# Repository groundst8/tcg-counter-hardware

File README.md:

# TCG Counter Hardware

## Components

[TI RF430FRL152H](https://www.ti.com/lit/ds/symlink/rf430frl152h.pdf?ts=1718074976833&ref_url=https%253A%252F%252Fwww.ti.com%252Fproduct%252FRF430FRL152H)
- ISO 15693
- NfcV
- 1.5V passivey powered
- 8 bit GPIO
- I2c
- +/- 400 uA GPIO current, 500 uA max all I/O 0.15V voltage drop

[Ynvisible D0432G02V01](https://assets-global.website-files.com/5f7f21e12602d912658dce12/62207f04e89fc72369fa582a_D0432G02V01-V1.0.pdf)
- 7 Segment E-Paper Display
- +/- 1.5V operating voltage
- 0.81 uA steady state current, all segments on
- ~3.25 mA (datasheet says 2.92 mA) peak current all segments; ~1.25 mA peak / segment

[TI TCAL9539](https://www.ti.com/lit/ds/symlink/tcal9539.pdf)
- Low-Voltage 16-Bit I2c Expander
- I/Os backpowered protected

## Constraints

### Harvested Power

Table 4 from [Frequently asked questions for RF430FRL15xH devices](https://www.ti.com/lit/an/sloa247c/sloa247c.pdf) shows the maximum harvested power available when using the using the TRF7970AEVM with a 5-V power supply as the tag reader. It is also mentioned that the current that can be supplied depends on the reader distance to the tag. 

## Ynvisible Display Testing

Twenty minute timelapse test to evaluation if the Ynvisible 7 segment display keeps readable contrast over a 20 minute period without power. Twenty minutes was chosen as the upper end of how long a counter would go without being updated. Twenty minutes is the length of the average Magic The Gathering standard format game. Commander games go longer but generally counters are updated over the course of the game which would provide the refresh without requiring additional effort.

## Development Board Prototyping

### Iteration 1

- GoodTag11
  - Open source hardware design
  - PCB & SMT assembly by JLCPCB
  - Through hole headers hand soldered by yours truly
- Ynvisible E-Paper Display Kit Adapter

#### Issues
- E-paper display backpowering RF430FRL152H via GPIO ESD diodes in no power state
  - GPIOs do not remain high-Z and display loses contrast
- TimerA0 low power delays not working in ROM patch operating mode
  - Temporarily doing delays on smartphone side
 
## Iteration 2

- Put two 4 channel TMUX1511 analog switches between GPIOs and display
  - Enabled when have power and disabled when no power is applied
  - Fixes display contrast loss issue from Iteration 1

#### Issues
- GPIO Port1.7 is used by ROM code to indicate operating mode and doesn't seem available for display use in ROM patch mode
- Ultimately would be more useful with two 7 segment digits, could potentially use single chip TCAL9539 GPIO expanded that should also remain high-Z with no power
  - Would be fewer parts than the TMUX1511 solution and give greater capability
- Peak current consumption of display was more than anticiapted per segment
  - Look into handling larger peak current with appropriately sized capacitor

Ynvisible provided segment switching current decay curves which are shown below modeled with exponential decay functions. The raw data is available in 1vs7segs.xlsx. I was anticipating the single segment switching current to be lower so will need to do some additional testing and measurement to determine if enough energy will be harvested to do the switching.

## Iteration 3

- Switched to RF430FRL152HEVM dev board
  - Can program with MSP-FET programmer via JTAG
  - Work around issue programming GoodTag11 with GoodV over the air not working with NFC only ROM firmware
- Switched from TMUX1511s to TCAL9539 for GPIO expansion and backpower protection
- Switched to Ynvisible 2 digit 7 segment display

#### Issues
- Currently powered from MSP-FET source
  - Need to do testing and see if can find solution to passively power from RF field in a way that is economically viable
- Need to get JTAG level transalation working so can switch back to GoodTag11 and custom PCB instead of dev board and use MSP-FET programmer

## Iteration 4

- Switched back to GoodTag11 from RF430FRL152HEVM dev board
- JTAG Level Translation & JTAG debugging working
  - Using SN74AXC4T774 Evaluation Module with TCK, TDI, TMS, TDO, and RST signals 3.3v <-> 1.5v
  - Replaced some 10pF capacitors that should have been 10nF and were preventing JTAG debugging from working
- EnergyTrace working

#### Issues
- Evaluate passive power ability to drive display
- Complete PCB layouts for mainboard and JTAG translation board

## Iteration 5 - v1.0.0

### JLCPCB PCB with rails/fiducials for assembly

### Board with display attached and functioning

#### Issues
- Forgot pull-up resistors for RESET and INT pins on TCAL
- Firmware updating all segments in parallel is causing brownouts, look into sequential segment updating

## Electrical Engineering

[Jupyter Notebook](display.ipynb)

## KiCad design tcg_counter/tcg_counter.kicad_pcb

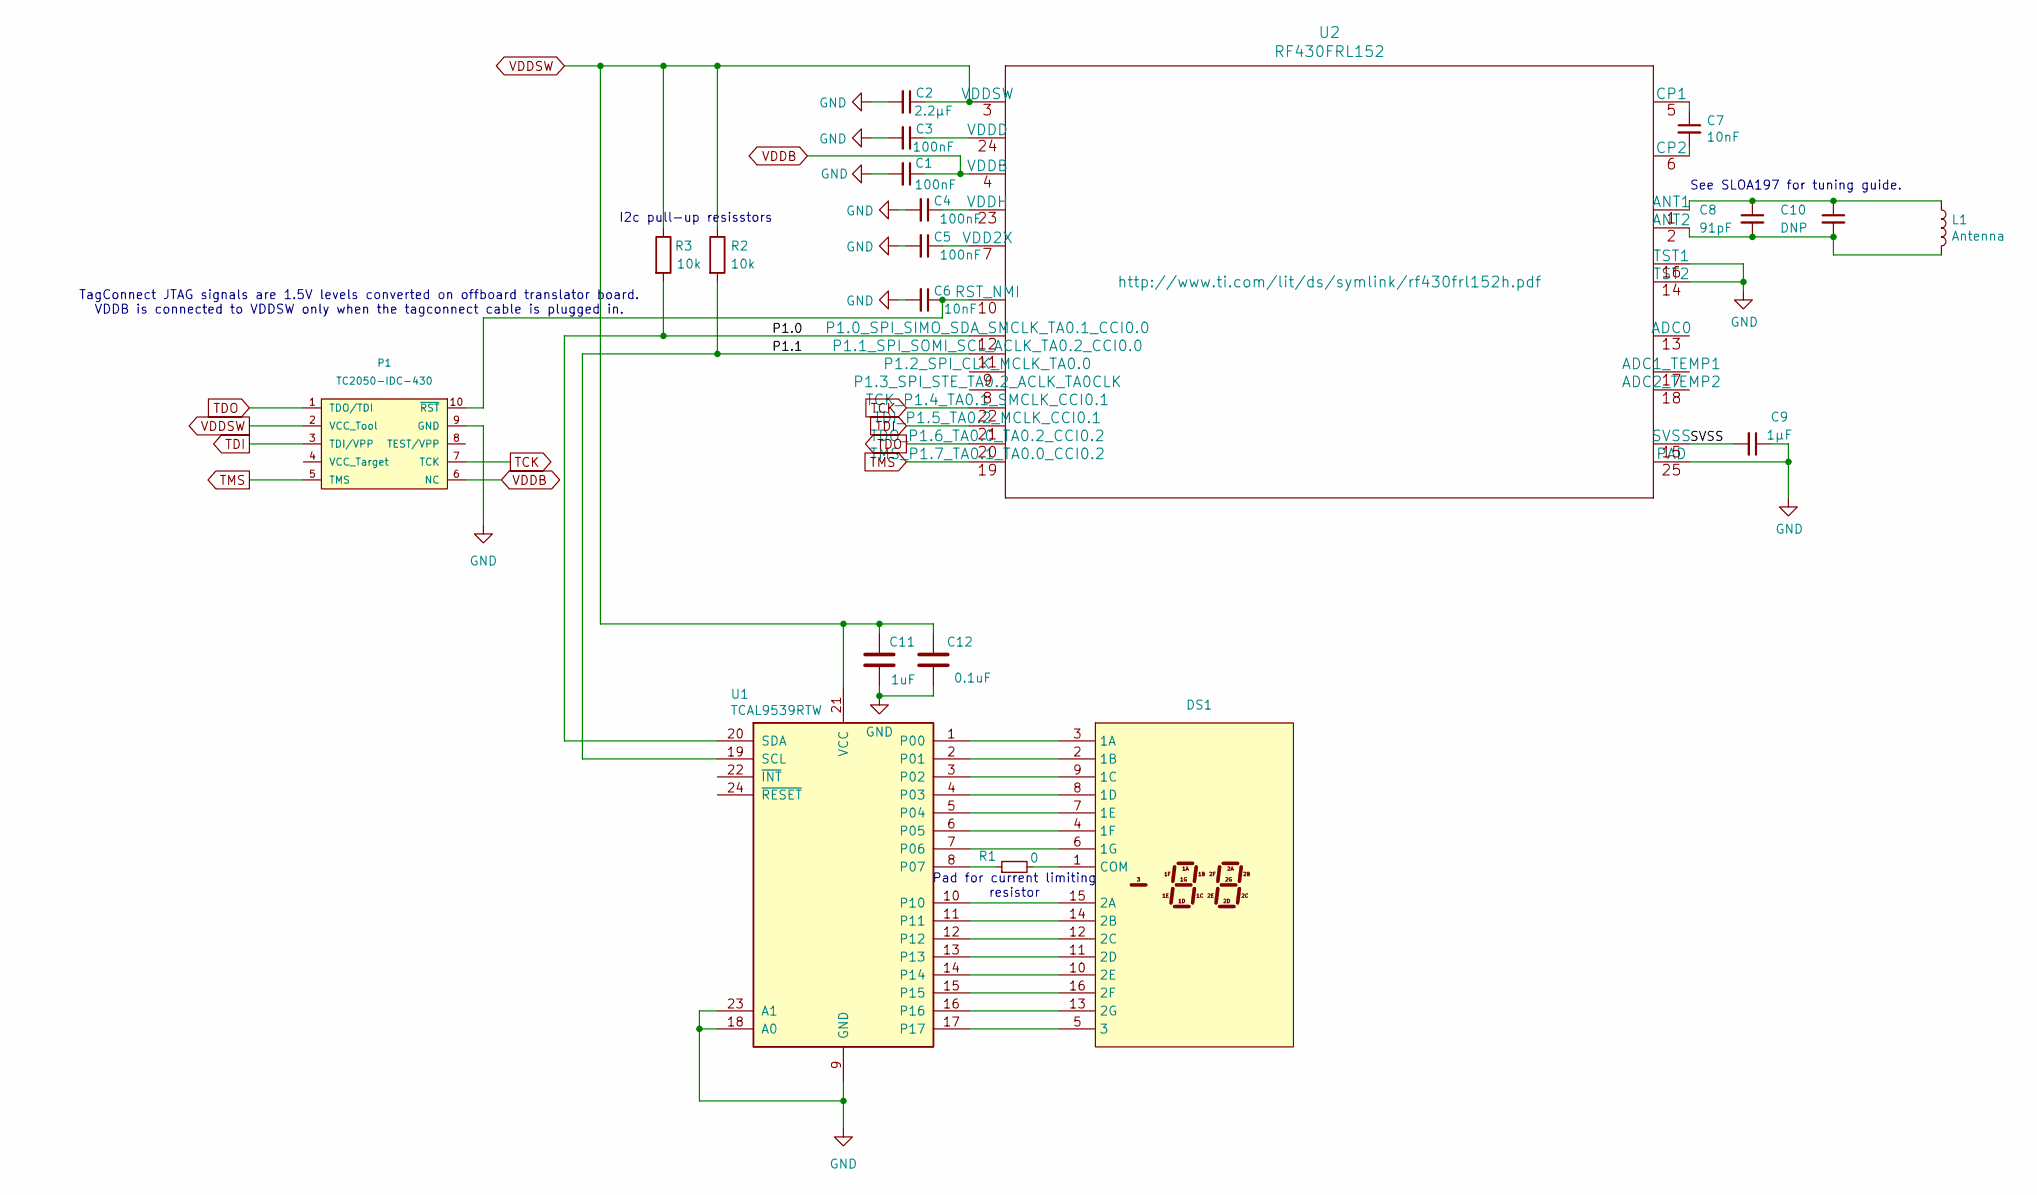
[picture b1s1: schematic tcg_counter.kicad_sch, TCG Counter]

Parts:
C1, C3, C4, C5: 100nF; C_0402_1005Metric
C2: 2.2µF; C_0402_1005Metric
C6, C7: 10nF; C_0402_1005Metric
C8: 91pF; C_0402_1005Metric
C9: 1µF; C_0402_1005Metric
C10: DNP; C_0402_1005Metric
C11: 1uF; C_0402_1005Metric
C12: 0.1uF; C_0402_1005Metric
DS1: D0430G02V01
L1: Antenna; GW10ANT
P1: TC2050-IDC-430; Tag-Connect_TC2050-IDC-NL_2x05_P1.27mm_Vertical_with_bottom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
R1: 0; R_0402_1005Metric
R2, R3: 10k; R_0402_1005Metric
U1: TCAL9539RTW; TI_RTW24_4x4mm_EP2.2mm
U2: RF430FRL152; RF430FRL152H

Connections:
/P1.0: R3.2, U1.20 (SDA), U2.12 (P1.0_SPI_SIMO_SDA_SMCLK_TA0.1_CCI0.0)
/P1.1: R2.2, U1.19 (SCL), U2.11 (P1.1_SPI_SOMI_SCL_ACLK_TA0.2_CCI0.0)
/SVSS: C9.2, U2.15 (SVSS)
GND: C1.2, C2.2, C3.2, C4.2, C5.2, C6.2, C9.1, C11.2, C12.2, P1.9 (GND), U1.9 (GND), U1.18 (A0), U1.23 (A1), U1.25, U2.14 (TST2), U2.16 (TST1), U2.25 (PAD)
unnamed: DS1.3 (1A), U1.1 (P00)
unnamed: DS1.2 (1B), U1.2 (P01)
unnamed: DS1.9 (1C), U1.3 (P02)
unnamed: DS1.8 (1D), U1.4 (P03)
unnamed: DS1.7 (1E), U1.5 (P04)
unnamed: DS1.4 (1F), U1.6 (P05)
unnamed: DS1.6 (1G), U1.7 (P06)
unnamed: DS1.15 (2A), U1.10
unnamed: DS1.14 (2B), U1.11
unnamed: DS1.12 (2C), U1.12
unnamed: DS1.11 (2D), U1.13
unnamed: DS1.10 (2E), U1.14
unnamed: DS1.16 (2F), U1.15
unnamed: DS1.13 (2G), U1.16
unnamed: DS1.5 (3), U1.17
unnamed: DS1.1 (COM), R1.2
unnamed: C6.1, P1.10 (~RST), U2.10 (RST_NMI)
unnamed: R1.1, U1.8 (P07)
unnamed: C8.1, C10.1, L1.1, U2.1 (ANT1)
unnamed: C8.2, C10.2, L1.2, U2.2 (ANT2)
unnamed: C7.1, U2.5 (CP1)
unnamed: C7.2, U2.6 (CP2)
unnamed: C5.1, U2.7 (VDD2X)
unnamed: C3.1, U2.24 (VDDD)
unnamed: C4.1, U2.23 (VDDH)
TCK: P1.7 (TCK), U2.22 (TCK_P1.4_TA0.1_SMCLK_CCI0.1)
TDI: P1.3 (TDI/VPP), U2.21 (TDI_P1.5_TA0.2_MCLK_CCI0.1)
TDO: P1.1 (TDO/TDI), U2.20 (TDO_P1.6_TA0.0_TA0.2_CCI0.2)
TMS: P1.5 (TMS), U2.19 (TMS_P1.7_TA0.1_TA0.0_CCI0.2)
VDDB: C1.1, P1.6 (NC), U2.4 (VDDB)
VDDSW: C2.1, C11.1, C12.1, P1.2 (VCC_Tool), R2.1, R3.1, U1.21 (VCC), U2.3 (VDDSW)

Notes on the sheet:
Pad for current limiting resistor
I2c pull-up resisstors
TagConnect JTAG signals are 1.5V levels converted on offboard translator board. VDDB is connected to VDDSW only when the tagconnect cable is plugged in.
See SLOA197 for tuning guide.

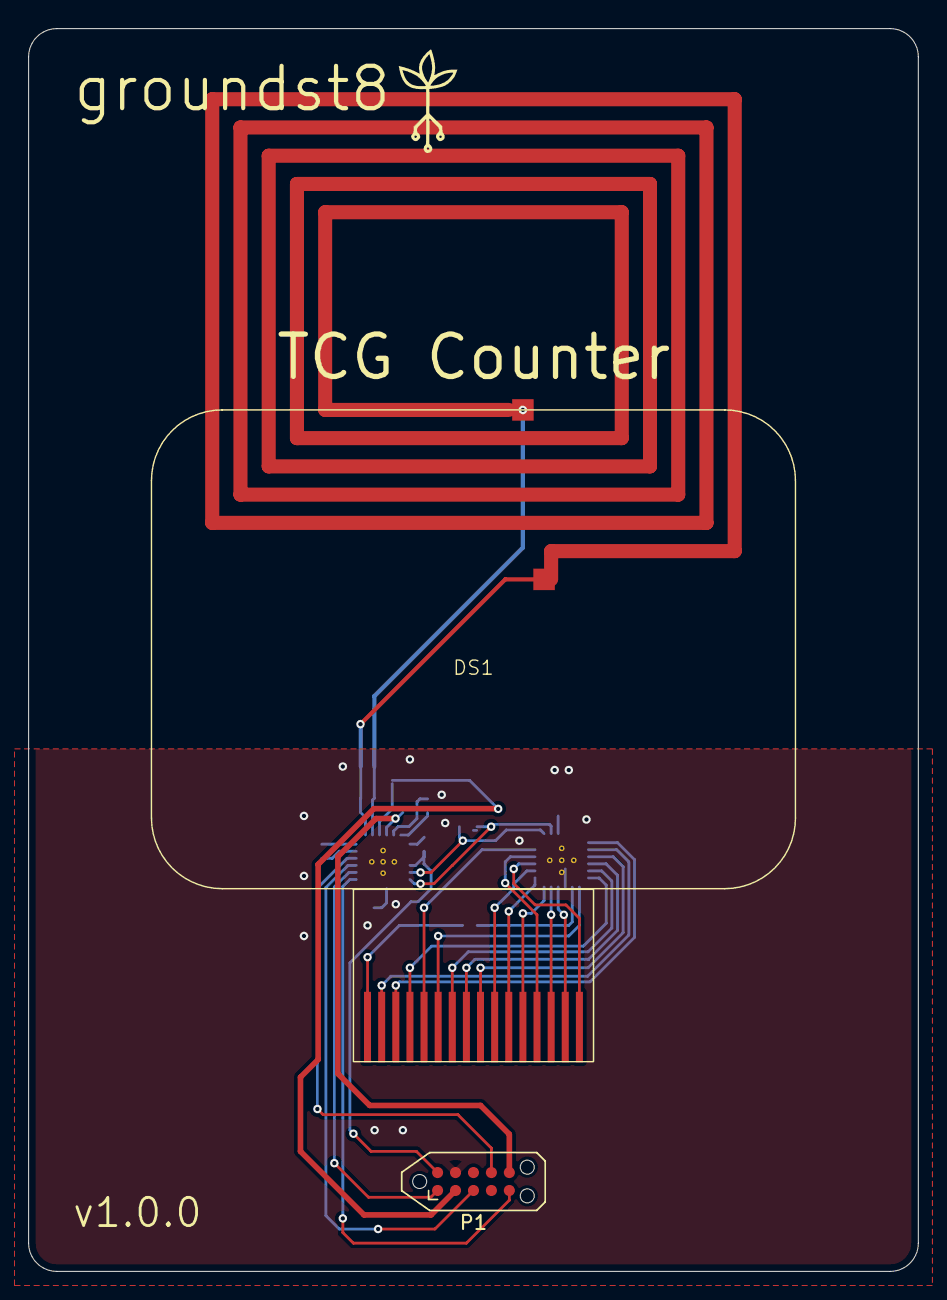
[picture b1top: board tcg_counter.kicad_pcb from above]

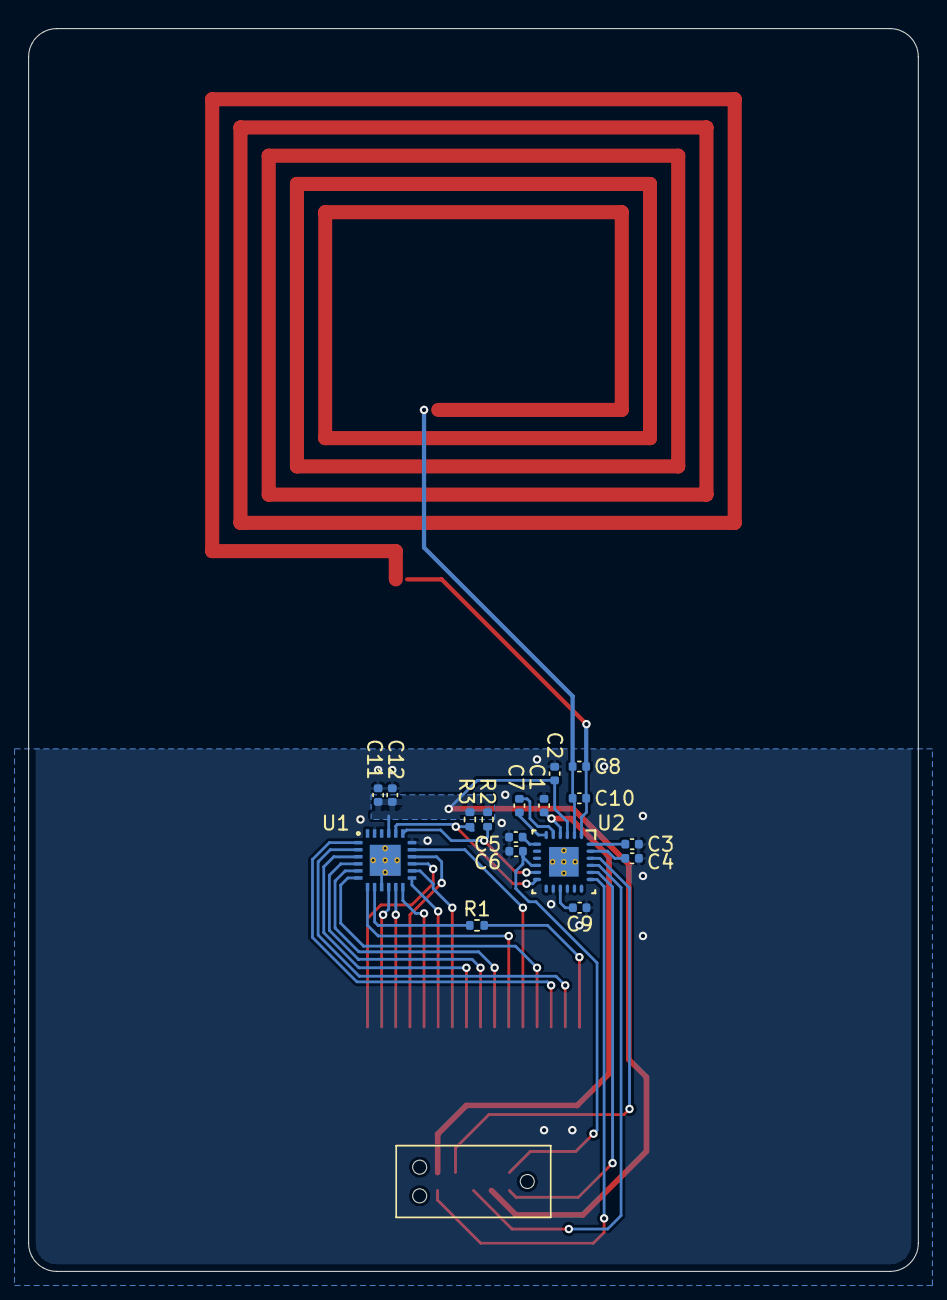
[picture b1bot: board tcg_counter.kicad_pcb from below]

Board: 2 copper layers, 63.0 x 88.0 mm, 20 parts (17 on the bottom side), 35 nets.

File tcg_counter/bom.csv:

"Reference","Value","Datasheet","Footprint","Qty","DNP"
"C1,C3,C4,C5","100nF","~","Capacitor_SMD:C_0402_1005Metric","4",""
"C2","2.2µF","~","Capacitor_SMD:C_0402_1005Metric","1",""
"C6,C7","10nF","~","Capacitor_SMD:C_0402_1005Metric","2",""
"C8","91pF","~","Capacitor_SMD:C_0402_1005Metric","1",""
"C9","1µF","~","Capacitor_SMD:C_0402_1005Metric","1",""
"C10","DNP","~","Capacitor_SMD:C_0402_1005Metric","1",""
"C11","1uF","~","Capacitor_SMD:C_0402_1005Metric","1",""
"C12","0.1uF","~","Capacitor_SMD:C_0402_1005Metric","1",""
"DS1","~","","Library:D0430G02V01","1",""
"L1","Antenna","~","footprints:GW10ANT","1",""
"P1","TC2050-IDC-430","","Connector:Tag-Connect_TC2050-IDC-NL_2x05_P1.27mm_Vertical_with_bottom_clip","1",""
"R1","0","~","Resistor_SMD:R_0402_1005Metric","1",""
"R2,R3","10k","~","Resistor_SMD:R_0402_1005Metric","2",""
"U1","TCAL9539RTW","http://www.ti.com/lit/ds/symlink/tca9539.pdf","TIFootprints:TI_RTW24_4x4mm_EP2.2mm","1",""
"U2","RF430FRL152","http://www.ti.com/lit/ds/symlink/rf430frl152h.pdf","footprints:RF430FRL152H","1",""

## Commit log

2024-06-11 Added components section
2024-06-21 Added v2 design tradeoffs
2024-06-21 Added I2C chip
2024-07-18 Added development board prototyping section
2024-10-01 Add initial jupyter notebook
2024-10-01 Try embedding notebook directly in readme
2024-10-01 Remove attempted embedding
2024-10-13 Add empty kicad project
2024-10-13 Mess around with qr code on silkscreen
2024-10-13 Added contacts for display
2024-10-19 Added iteration 1 section
2024-10-19 Added Iteration 2 section
2024-10-19 Added dispay symbol to schematic and update TCAL9539
2024-10-27 Added display segment switching current curves
2024-10-27 Added harvested power constraint section
2024-11-10 Added Ynvisible timelapse video link
2024-11-10 Added current decay plot
2024-11-10 Added display current measurements raw data
2024-11-24 Added iteration 3 hardware section
2025-01-21 Added antenna trace from goodtag
2025-02-12 Removed QR code
2025-02-26 Added iteration 4 hardware
2025-03-07 Added notebook for ynvisible current curves
2025-03-08 Added current limiting resistor
2025-03-08 Removed old p1.2 and p1.3 header connections
2025-03-09 Added decoupling capacitors on TCAL9539RTW
2025-03-10 Assigned footprints
2025-04-06 Work on pcb layout, added no fill zones
2025-04-20 Added tagconnect power signals
2025-04-20 Routing to antenna and some capacitors
2025-05-24 Finished traces, made new footprint for TCAL9539
2025-05-25 Cleaned up pad vias and solder paste
2025-06-06 v1.0 hardware revision
2025-06-13 Added v1.0.0 hardware section
